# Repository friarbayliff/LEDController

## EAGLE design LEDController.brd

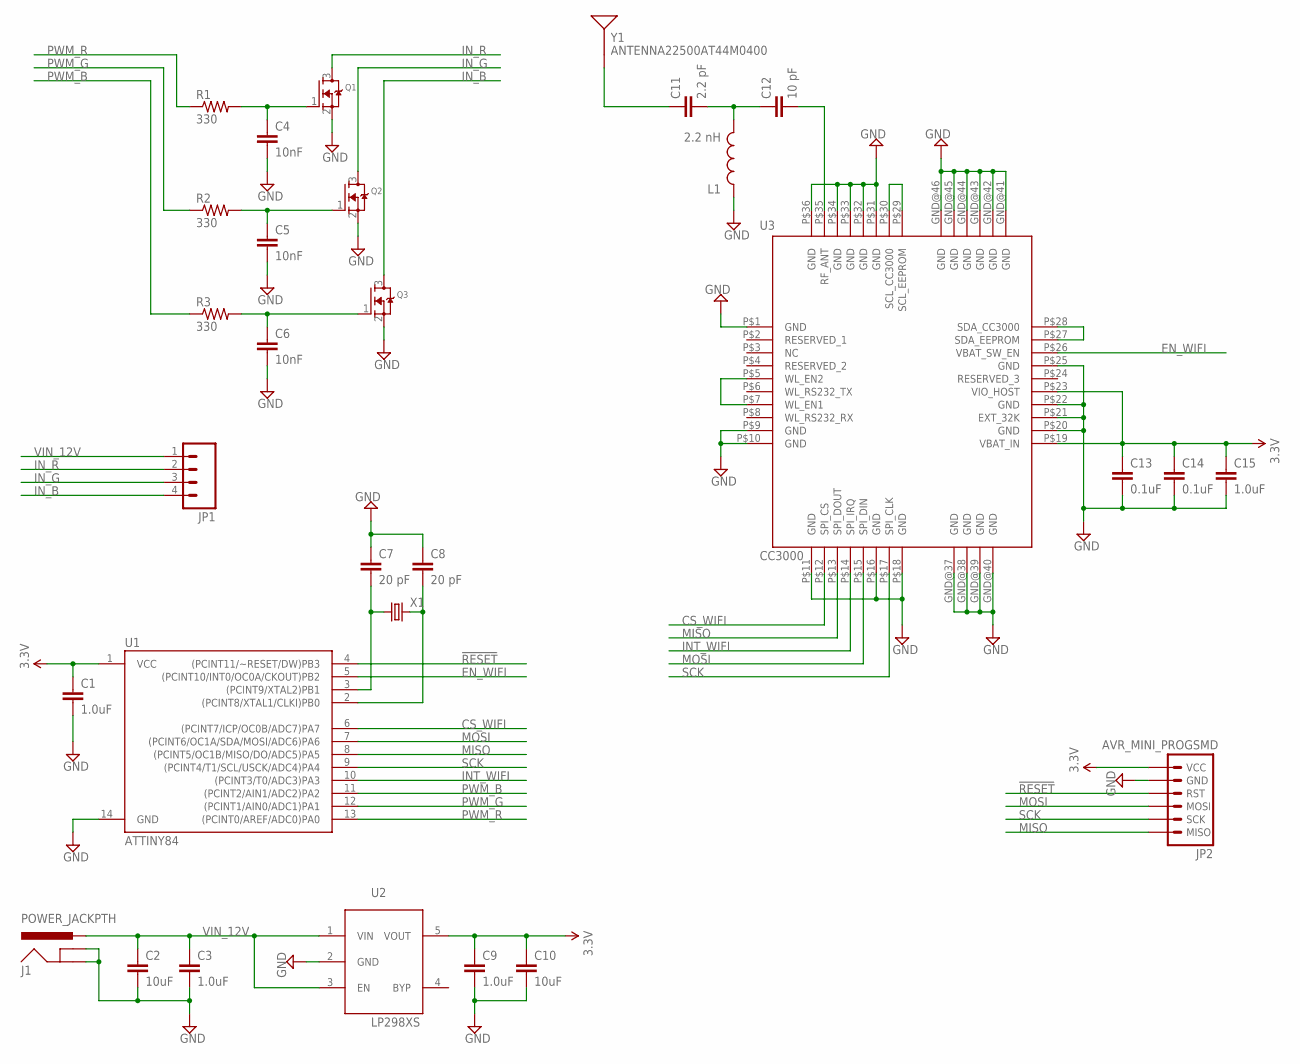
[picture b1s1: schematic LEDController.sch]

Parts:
C1, C3, C9, C15: 1.0uF; 0603-CAP
C2, C10: 10uF; 0603-CAP
C4, C5, C6: 10nF; 0603-CAP
C7, C8: 20 pF; 0603-CAP
C11: 2.2 pF; 0603-CAP
C12: 10 pF; 0603-CAP
C13, C14: 0.1uF; 0603-CAP
J1: POWER_JACKPTH; POWER_JACK_PTH
JP1: M04PTH; 1X04
JP2: AVR_MINI_PROGSMD; AVR_MINI_PROG
L1: 2.2 nH; 0603
Q1, Q2, Q3: MOSFET-NREFLOW; SOT23
R1, R2, R3: 330; 0603-RES
U1: ATTINY84; SO14
U2: LP298XS; SOT23-5L
U3: CC3000; QFN-46_CC3000
X1: CRYSTAL5X3; CRYSTAL-SMD-5X3
Y1: ANTENNA22500AT44M0400; ANTENNA-CHIP_2500AT44M0400

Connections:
3.3V: C1.1, C9.1, C10.1, C13.1, C14.1, C15.1, JP2.1 (VCC), U1.1 (VCC), U2.5 (VOUT), U3.P$19 (VBAT_IN), U3.P$23 (VIO_HOST)
!RESET: JP2.3 (RST), U1.4 ((PCINT11/~RESET/DW)PB3)
CS_WIFI: U1.6 ((PCINT7/ICP/OC0B/ADC7)PA7), U3.P$12 (SPI_CS)
EN_WIFI: U1.5 ((PCINT10/INT0/OC0A/CKOUT)PB2), U3.P$26 (VBAT_SW_EN)
GND: C1.2, C2.2, C3.2, C4.2, C5.2, C6.2, C7.1, C8.1, C9.2, C10.2, C13.2, C14.2, C15.2, J1.GND, J1.GNDBREAK, JP2.2 (GND), L1.1, Q1.2 (S), Q2.2 (S), Q3.2 (S), U1.14 (GND), U2.2 (GND), U3.GND@37 (GND), U3.GND@38 (GND), U3.GND@39 (GND), U3.GND@40 (GND), U3.GND@41 (GND), U3.GND@42 (GND), U3.GND@43 (GND), U3.GND@44 (GND), U3.GND@45 (GND), U3.GND@46 (GND), U3.P$1 (GND), U3.P$9 (GND), U3.P$10 (GND), U3.P$11 (GND), U3.P$16 (GND), U3.P$18 (GND), U3.P$20 (GND), U3.P$21 (EXT_32K), U3.P$22 (GND), U3.P$25 (GND), U3.P$31 (GND), U3.P$32 (GND), U3.P$33 (GND), U3.P$34 (GND), U3.P$36 (GND)
INT_WIFI: U1.10 ((PCINT3/T0/ADC3)PA3), U3.P$14 (SPI_IRQ)
IN_B: JP1.4, Q3.3 (D)
IN_G: JP1.3, Q2.3 (D)
IN_R: JP1.2, Q1.3 (D)
MISO: JP2.6 (MISO), U1.8 ((PCINT5/OC1B/MISO/DO/ADC5)PA5), U3.P$13 (SPI_DOUT)
MOSI: JP2.4 (MOSI), U1.7 ((PCINT6/OC1A/SDA/MOSI/ADC6)PA6), U3.P$15 (SPI_DIN)
unnamed: U3.P$27 (SDA_EEPROM), U3.P$28 (SDA_CC3000)
unnamed: U3.P$29 (SCL_EEPROM), U3.P$30 (SCL_CC3000)
unnamed: C6.1, Q3.1 (G), R3.2
unnamed: C5.1, Q2.1 (G), R2.2
unnamed: C4.1, Q1.1 (G), R1.2
unnamed: U3.P$5 (WL_EN2), U3.P$7 (WL_EN1)
unnamed: C11.2, C12.1, L1.2
unnamed: C11.1, Y1.FEED
unnamed: C7.2, U1.3 ((PCINT9/XTAL2)PB1), X1.1
unnamed: C8.2, U1.2 ((PCINT8/XTAL1/CLKI)PB0), X1.3 (2)
PWM_B: R3.1, U1.11 ((PCINT2/AIN1/ADC2)PA2)
PWM_G: R2.1, U1.12 ((PCINT1/AIN0/ADC1)PA1)
PWM_R: R1.1, U1.13 ((PCINT0/AREF/ADC0)PA0)
RF_ANT: C12.2, U3.P$35 (RF_ANT)
SCK: JP2.5 (SCK), U1.9 ((PCINT4/T1/SCL/USCK/ADC4)PA4), U3.P$17 (SPI_CLK)
VIN_12V: C2.1, C3.1, J1.PWR, JP1.1, U2.1 (VIN), U2.3 (EN)

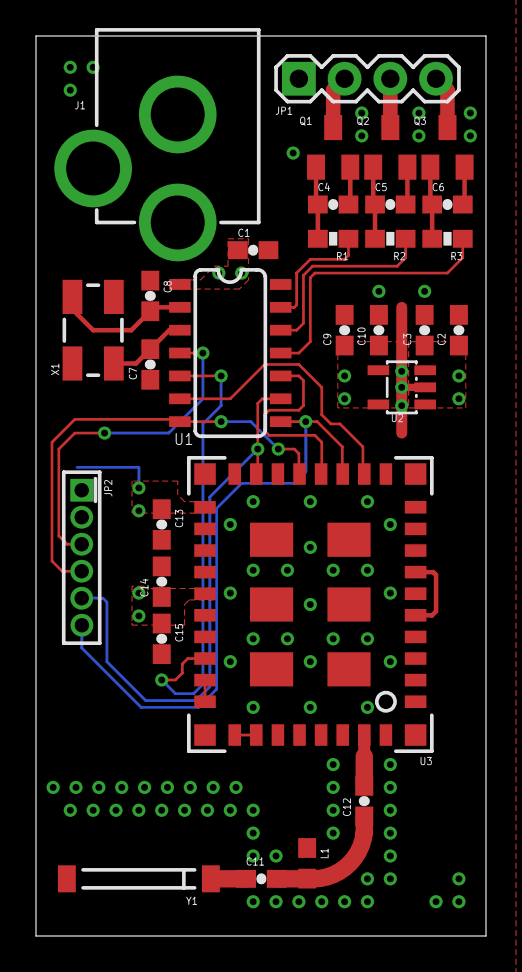
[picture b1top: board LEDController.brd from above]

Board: 2 copper layers, 25.0 x 50.0 mm, 30 parts (0 on the bottom side), 27 nets.

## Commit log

2014-07-10 Update
    Update before submission to fab
2014-07-14 BOM
    Bill of materials with DK part numbers

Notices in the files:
parts and their libraries:
SparkFun-RF: Licensing: Creative Commons ShareAlike 4.0 International - https://creativecommons.org/licenses/by-sa/4.0
